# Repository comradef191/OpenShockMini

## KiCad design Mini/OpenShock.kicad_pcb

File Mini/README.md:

## OpenShock Mini r1.3
Based on OpenShock Core V1.2

Customised OpenShock Core v1.2 derivative, with clearer component labelling & through-hole components intended to assist in manual low-volume assembly

#### CHANGES FROM REGULAR OPENSHOCK:
- Capacitors switched over to 0805 and clearly labelled for easy assembly
- Resistors have been converted to use standard through-hole resistors, with clearly marked resistance values
- Custom ESP32 footprint clearly marks essential pins, and makes soldering of the underside ground pads far easier
- Optional USB Mini-B footprint which may be populated if USB-C is beyond your ability to solder
- Standardised all buttons to use generic 6mm SPST buttons
- Now uses a pair of round 3mm THT LEDs rather than SMD ones; RGB LED remains unchanged
- 5V->3V3 Regulator switched to a slighty smaller and cheaper MSKSEMI AMS1117 rather than AMS (C5120796)
- Board footprint heavily reduced compared to V1.2, only slightly exceeding V2.2L

Important Notes:
- LCSC does not stock a 433MHz antenna that would be suitable for this board, thus you need to [order one from Aliexpress](https://aliexpress.com/item/1005005557947265.html); I reccomend one 28mm long, which rises up 6mm before bending.
- Install only one of the USB ports. If installing the USB-C port, R5 & R4 must be installed also.

#### Specs:
- ESP32-S3-WROOM-1
- USB-C or Mini-B
- Pinouts for several transmitters for DIY users
- In-built E-Stop button and AUX E-Stop port (3.5mm TRS jack)
- No USB-UART, uses built-in USB on ESP32-S3
- Low-Noise Texas Instruments 3.3v regulator
- Footprint 46 x 58mm

#### Bill of Materials:
|Component                     |QTY|LCSC P/N |Comment
|------------------------------|---|---------|-------|
|0805 Capacitor, 100nF         | 3 |C476766  |       |
|0805 Capacitor, 1uF           | 2 |C215803  |       |
|0805 Capacitor, 10uF          | 2 |C1713    |       |
|0805 Capacitor, 22uF          | 2 |C98190   |       |
|Through-Hole Resistor, 5.1k   | 4 |C58591   |       |
|Through-Hole Resistor, 10k    | 4 |C57436   |       |
|Through-Hole Resistor, 100k   | 1 |C58597   |       |
|LED, SMD; RGB (D1)            | 1 |C527089  |       |
|LED, Through-Hole; Red (D3)   | 1 |C440523  |       |
|LED, Through-Hole; Blue (D4)  | 1 |C2895474 |       |
|B5819W-SL Diode (D2)          | 1 |C8598    |       |
|Fuse, 1206 SMD, 250mW 800v    | 1 |C17888   |       |
|3.5mm Port (EStop Connector)  | 1 |C2689690 |       |
|SPST Buttons                  | 3 |C2837516 |       |
|AMS1117 Voltage Regulator     | 1 |C5120796 |       |
|ESP32-S3-WROOM-1 N16R8        | 1 |C2913202 |Reccomend [Aliexpress](https://www.aliexpress.com/item/1005006661866218.html)|
|DL-TX1-433M 433MHz Transmitter| 1 |C381160  |       |
|433MHz Antenna                | 1 | None :C |See Important Notes section|
|USB-C Connector               | 1 |C165948  |USE ONE OR THE OTHER.|
|USB Mini-B Connector          | 1 |C720612  |USE ONE OR THE OTHER.|

### Gallery

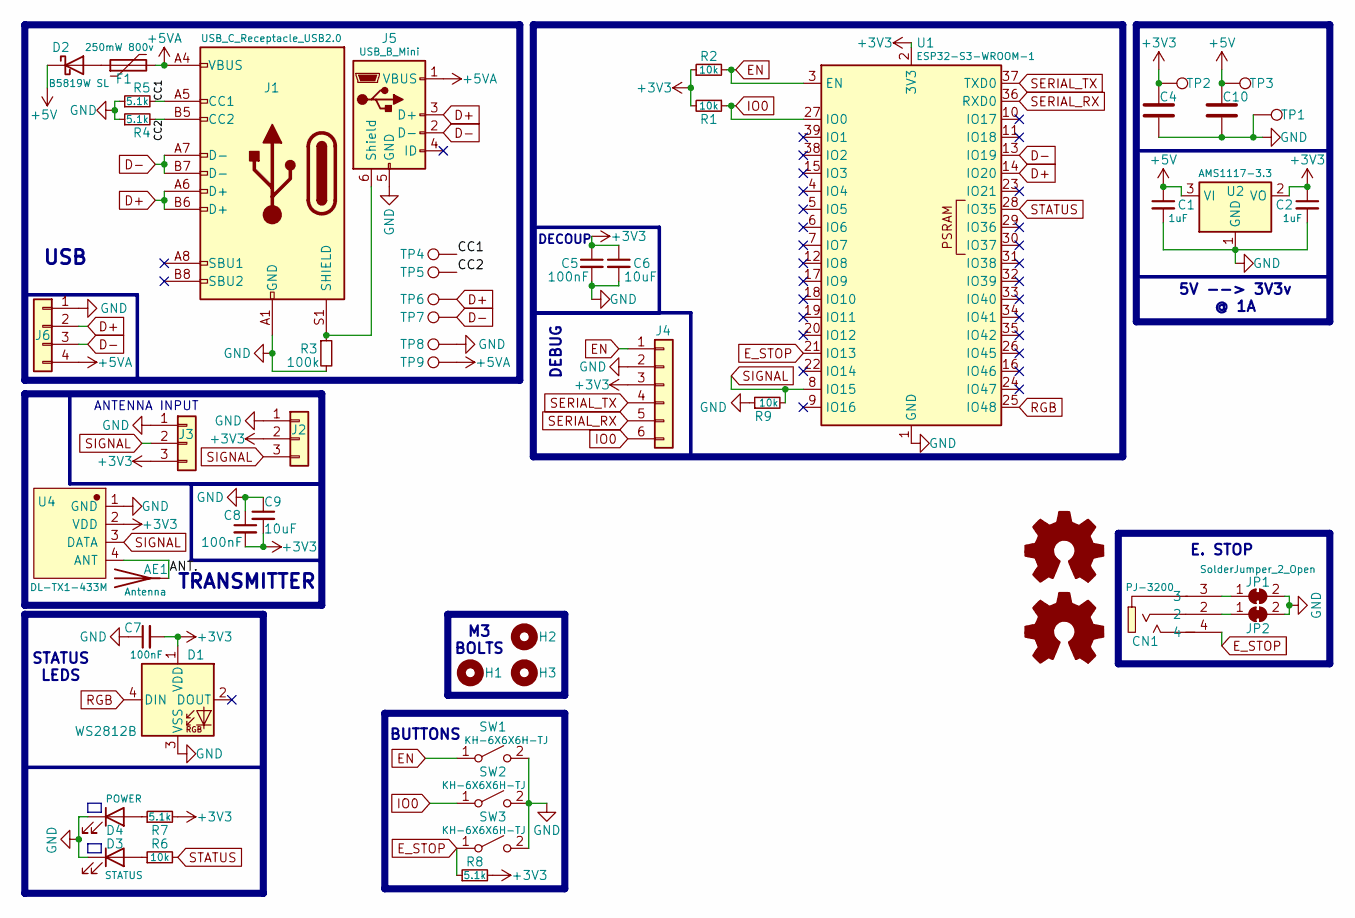
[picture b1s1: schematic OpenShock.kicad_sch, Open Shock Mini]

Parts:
AE1: Antenna; PinHeader_1x01_P2.54mm_Vertical
C1, C2: 1uF; C_0805_2012Metric_Pad1.18x1.45mm_HandSolder; LCSC C215803
C4, C10: 22uF; C_0805_2012Metric_Pad1.18x1.45mm_HandSolder; LCSC C98190
C5, C7, C8: 100nF; C_0805_2012Metric_Pad1.18x1.45mm_HandSolder; LCSC C476766
C6, C9: 10uF; C_0805_2012Metric_Pad1.18x1.45mm_HandSolder; LCSC C1713
CN1: PJ-3200; AUDIO-TH_PJ-3200; LCSC C2689690
D1: WS2812B; LED_WS2812B-Mini_3.5x3.5mm_P1.75mm; LCSC C527089
D2: B5819W SL; D_SOD-123; LCSC C8598
D3: STATUS; LED_D3.0mm; LCSC C440523
D4: POWER; LED_D3.0mm; LCSC C2895474
F1: 250mW 800v; Fuse_1206_3216Metric_Pad1.42x1.75mm_HandSolder; LCSC C17888
H1, H2, H3: MountingHole; MountingHole_3.2mm_M3_ISO7380
J1: USB_C_Receptacle_USB2.0; HRO-TYPE-C-31-M-12-HandSoldering_ABPads; LCSC C165948
J2, J3: Conn_01x03; PinHeader_1x03_P2.54mm_Vertical
J4: Conn_01x06; PinHeader_1x06_P2.54mm_Vertical
J5: USB_B_Mini; MICRO-USB-TH_UX-150-ARG4; LCSC C720612
J6: Conn_01x04; PinHeader_1x04_P2.54mm_Vertical
JP1, JP2: SolderJumper_2_Open; SolderJumper-2_P1.3mm_Bridged_RoundedPad1.0x1.5mm
R1, R2, R6, R9: 10k; THT-Resistor_Customised
R3: 100k; THT-Resistor_Customised
R4, R5, R7, R8: 5.1k; THT-Resistor_Customised
SW1, SW2, SW3: KH-6X6X6H-TJ; SW_PUSH_6mm; LCSC C2837516
TP1, TP2, TP3, TP4, TP5, TP6, TP7, TP8, TP9: TestPoint; TestPoint_Pad_D1.5mm
U1: ESP32-S3-WROOM-1; LCSC C2913202
U2: AMS1117-3.3; SOT-89-3_Handsoldering; LCSC C5120796
U4: DL-TX1-433M; WIELM-TH_DL-TX1-433M; LCSC C381160

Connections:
+3V3: C2.1, C4.1, C5.1, C6.1, C7.2, C8.2, C9.2, D1.1 (VDD), J2.2, J3.3, J4.3, R1.2, R2.1, R7.2, R8.2, TP2.1, U1.2 (3V3), U2.2 (VO), U4.2 (VDD)
+5V: C1.1, C10.1, D2.1 (K), TP3.1, U2.3 (VI)
+5VA: F1.2, J1.A4 (VBUS), J1.A9 (VBUS), J1.B4 (VBUS), J1.B9 (VBUS), J5.1 (VBUS), J6.4, TP9.1
/ANT.: AE1.1 (A), U4.4 (ANT)
/CC1: J1.A5 (CC1), R5.2, TP4.1
/CC2: J1.B5 (CC2), R4.2, TP5.1
D+: J1.A6 (D+), J1.B6 (D+), J5.3 (D+), J6.2, TP6.1, U1.14 (IO20)
D-: J1.A7 (D-), J1.B7 (D-), J5.2 (D-), J6.3, TP7.1, U1.13 (IO19)
EN: J4.1, R2.2, SW1.1 (A), U1.3 (EN)
E_STOP: CN1.4, R8.1, SW3.1 (A), U1.21 (IO13)
GND: C1.2, C2.2, C4.2, C5.2, C6.2, C7.1, C8.1, C9.1, C10.2, D1.3 (VSS), D3.1 (K), D4.1 (K), J1.A1 (GND), J1.A12 (GND), J1.B1 (GND), J1.B12 (GND), J2.1, J3.1, J4.2, J5.5 (GND), J6.1, JP1.2 (B), JP2.2 (B), R3.2, R4.1, R5.1, R9.1, SW1.2 (B), SW2.2 (B), SW3.2 (B), TP1.1, TP8.1, U1.1 (GND), U1.40 (GND), U1.41 (GND), U2.1 (GND), U4.1 (GND)
IO0: J4.6, R1.1, SW2.1 (A), U1.27 (IO0)
unnamed: D2.2 (A), F1.1
unnamed: D3.2 (A), R6.1
unnamed: D4.2 (A), R7.1
unnamed: J1.S1 (SHIELD), J5.6 (Shield), R3.1
unnamed: CN1.3, JP1.1 (A)
unnamed: CN1.2, JP2.1 (A)
RGB: D1.4 (DIN), U1.25 (IO48)
SERIAL_RX: J4.5, U1.36 (RXD0)
SERIAL_TX: J4.4, U1.37 (TXD0)
SIGNAL: J2.3, J3.2, R9.2, U1.8 (IO15), U4.3 (DATA)
STATUS: R6.2, U1.28 (IO35)

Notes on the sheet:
ANTENNA INPUT
TRANSMITTER
BUTTONS
M3 BOLTS
5V --> 3V3v @ 1A
DECOUP
STATUS LEDS
E. STOP
USB
DEBUG

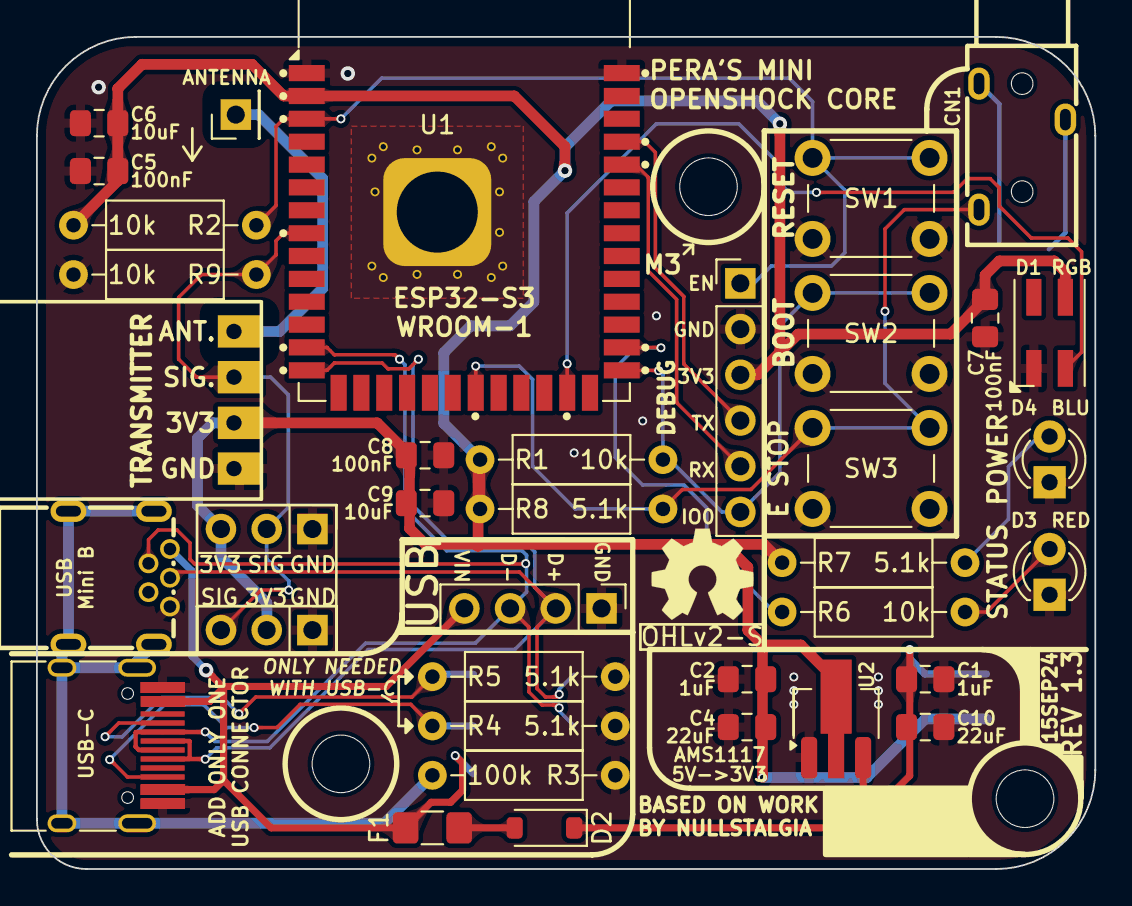
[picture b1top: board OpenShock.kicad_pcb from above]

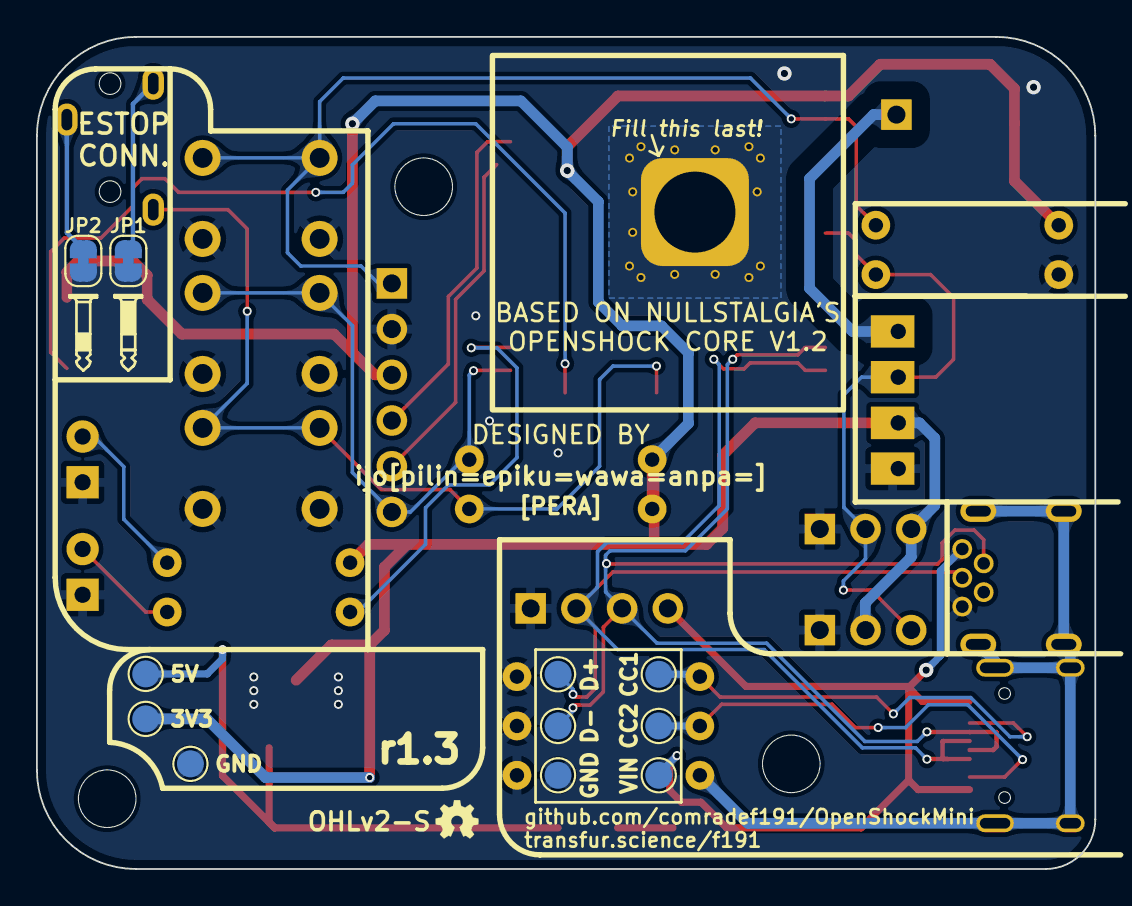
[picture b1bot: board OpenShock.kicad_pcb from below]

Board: 2 copper layers, 58.8 x 46.2 mm, 51 parts (11 on the bottom side), 23 nets.

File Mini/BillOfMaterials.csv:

"Value","Qty","LCSC"
"Antenna","1",""
"1uF","2","C5189821"
"22uF","4","C7432770"
"100nF","3","C6119861"
"10uF","2","C380316"
"WS2812B","1","C527089"
"B5819W SL","1","C8598"
"STATUS","1","C440523"
"POWER","1","C2895474"
"250mW 800v","1","C17888"
"MountingHole","2",""
"USB_C_Receptacle_USB2.0","1","C165948"
"Conn_01x03","2",""
"Conn_01x06","1",""
"Conn_01x04","1",""
"10k","3",""
"100k","1",""
"5.1k","5",""
"KH-6X6X6H-TJ","3","C2837516"
"ESP32-S3-WROOM-1","1","C2913204"
"TPS7A2033PDBVR","1","C2862740"
"DL-TX1-433M","1","C381160"

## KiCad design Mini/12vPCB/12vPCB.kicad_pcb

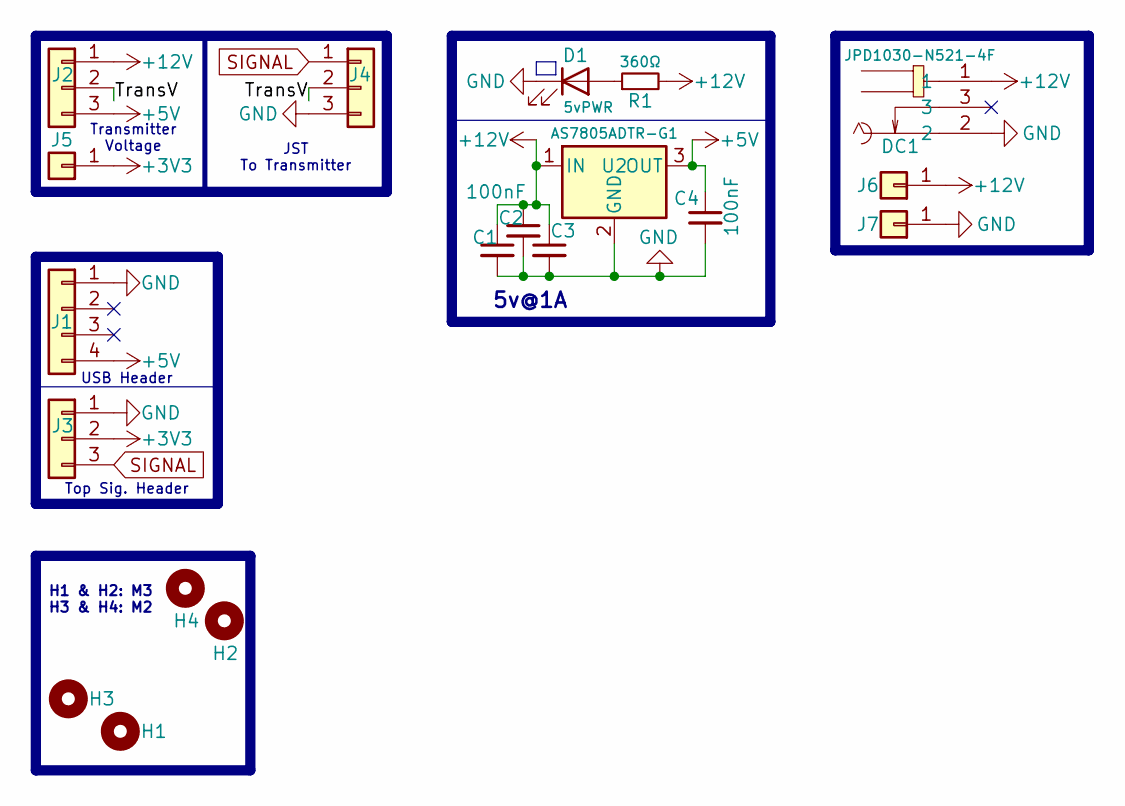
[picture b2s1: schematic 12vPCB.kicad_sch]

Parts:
C1, C2, C3, C4: 100nF; C_0603_1608Metric_Pad1.08x0.95mm_HandSolder; LCSC C6119861
D1: 5vPWR; LED_D3.0mm; LCSC C440523
DC1: JPD1030-N521-4F; DC-IN-TH_JPD1030-N521-4F; LCSC Part C426213
H1, H2: MountingHole; MountingHole_3.2mm_M3_ISO7380
H3, H4: MountingHole; MountingHole_2.2mm_M2_ISO7380
J1: Conn_01x04; PinSocket_1x04_P2.54mm_Vertical
J2: Conn_01x03; PinHeader_1x03_P2.54mm_Vertical
J3: Conn_01x03; PinSocket_1x03_P2.54mm_Vertical
J4: Conn_01x03; JST-XH 03 - Endstop
J5, J6, J7: Conn_01x01; PinHeader_1x01_P2.54mm_Vertical
R1: 360Ω; THT-Resistor_Customised
U2: AS7805ADTR-G1; TO-252-2; LCSC C294595

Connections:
+3V3: J3.2, J5.1
+5V: C4.1, J1.4, J2.3, U2.3 (OUT)
+12V: C1.1, C2.1, C3.1, DC1.1, J2.1, J6.1, R1.2, U2.1 (IN)
/TransV: J2.2, J4.2
GND: C1.2, C2.2, C3.2, C4.2, D1.1 (K), DC1.2, J1.1, J3.1, J4.3, J7.1, U2.2 (GND)
unnamed: D1.2 (A), R1.1
SIGNAL: J3.3, J4.1

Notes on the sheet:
Transmitter Voltage
USB Header
Top Sig. Header
JST To Transmitter
H1 & H2: M3 H3 & H4: M2
5v@1A

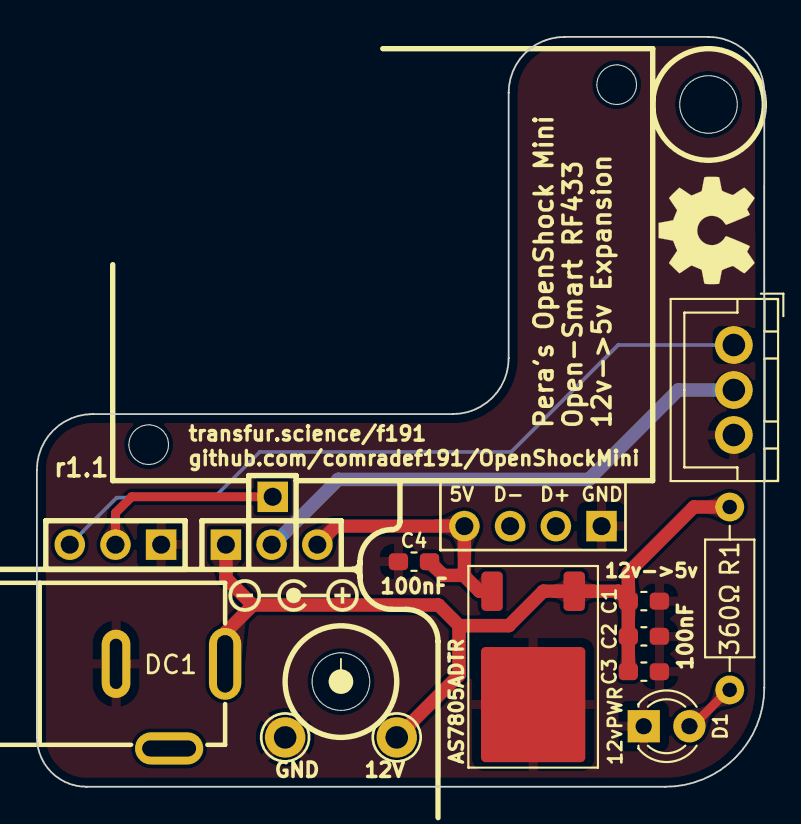
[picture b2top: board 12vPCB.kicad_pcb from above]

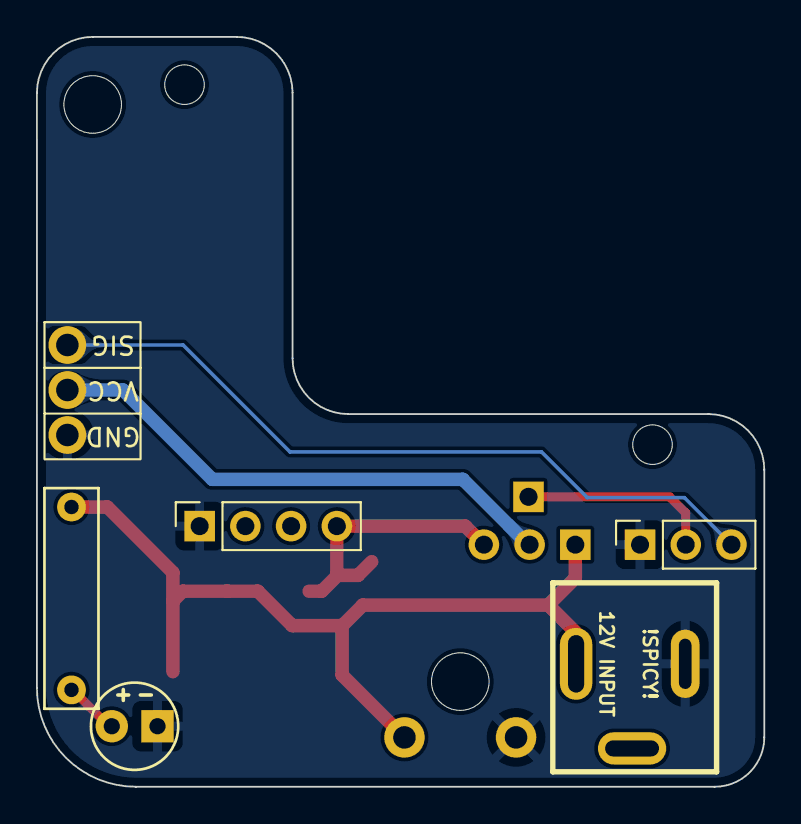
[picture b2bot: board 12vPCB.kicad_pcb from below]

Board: 2 copper layers, 40.4 x 41.7 mm, 20 parts (2 on the bottom side), 7 nets.

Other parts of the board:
U1: Open-Smart RF433 Module

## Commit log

2024-06-21 Add Mini files (WIP)
2024-06-21 Schematic Fixes & Add Title Blocks
2024-06-21 Update rear silkscreen
2024-06-21 Finalisation of PCB files
2024-06-21 Add schematic & 3D Model (TODO: Case / Mounting)
2024-06-21 also a gerbers zip. ill move this at Some Point:tm:
2024-06-21 Flesh-Out ReadMe w/ images & info
2024-06-21 Schematic Fixes + Add BoM
2024-06-21 R1.1; Upgrade from AMS1117 to Low-Noise TI chip; TPS7A2033PDBVR, 300mA output
    Added locally saved images of board, rather than Github cache.
2024-06-24 r1.2; Board reshuffled for ease of add-on design, plus ESP32 soldering
2024-07-07 New revision; Board fixes
2024-09-15 Cleanup
2024-09-15 New Revision.

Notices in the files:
Mini/OpenShock.kicad_pcb:
CERN OHL v2 - S
